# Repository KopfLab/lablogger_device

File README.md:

# *labLogger*

This repository holds the code, schematics, and documentation to build lab loggers. All content of this repository is free to use for noncommercial research and development efforts as outlined in the terms of the included [LICENSE file](LICENSE.md).

To cite ***labLogger*** in publications use:

> Kopf S, 2026. _labLogger: a Modular Internet Controllable LAB Equipment Logger_. <https://github.com/KopfLab/lablogger_device>

A BibTeX entry for LaTeX users is

```
@Manual{
  microLogger,
  title = {labLogger: a Modular Internet Controllable LAB Equipment Logger},
  author = {Sebastian Kopf},
  year = {2026},
  url = {https://github.com/KopfLab/lablogger_device}
}
```

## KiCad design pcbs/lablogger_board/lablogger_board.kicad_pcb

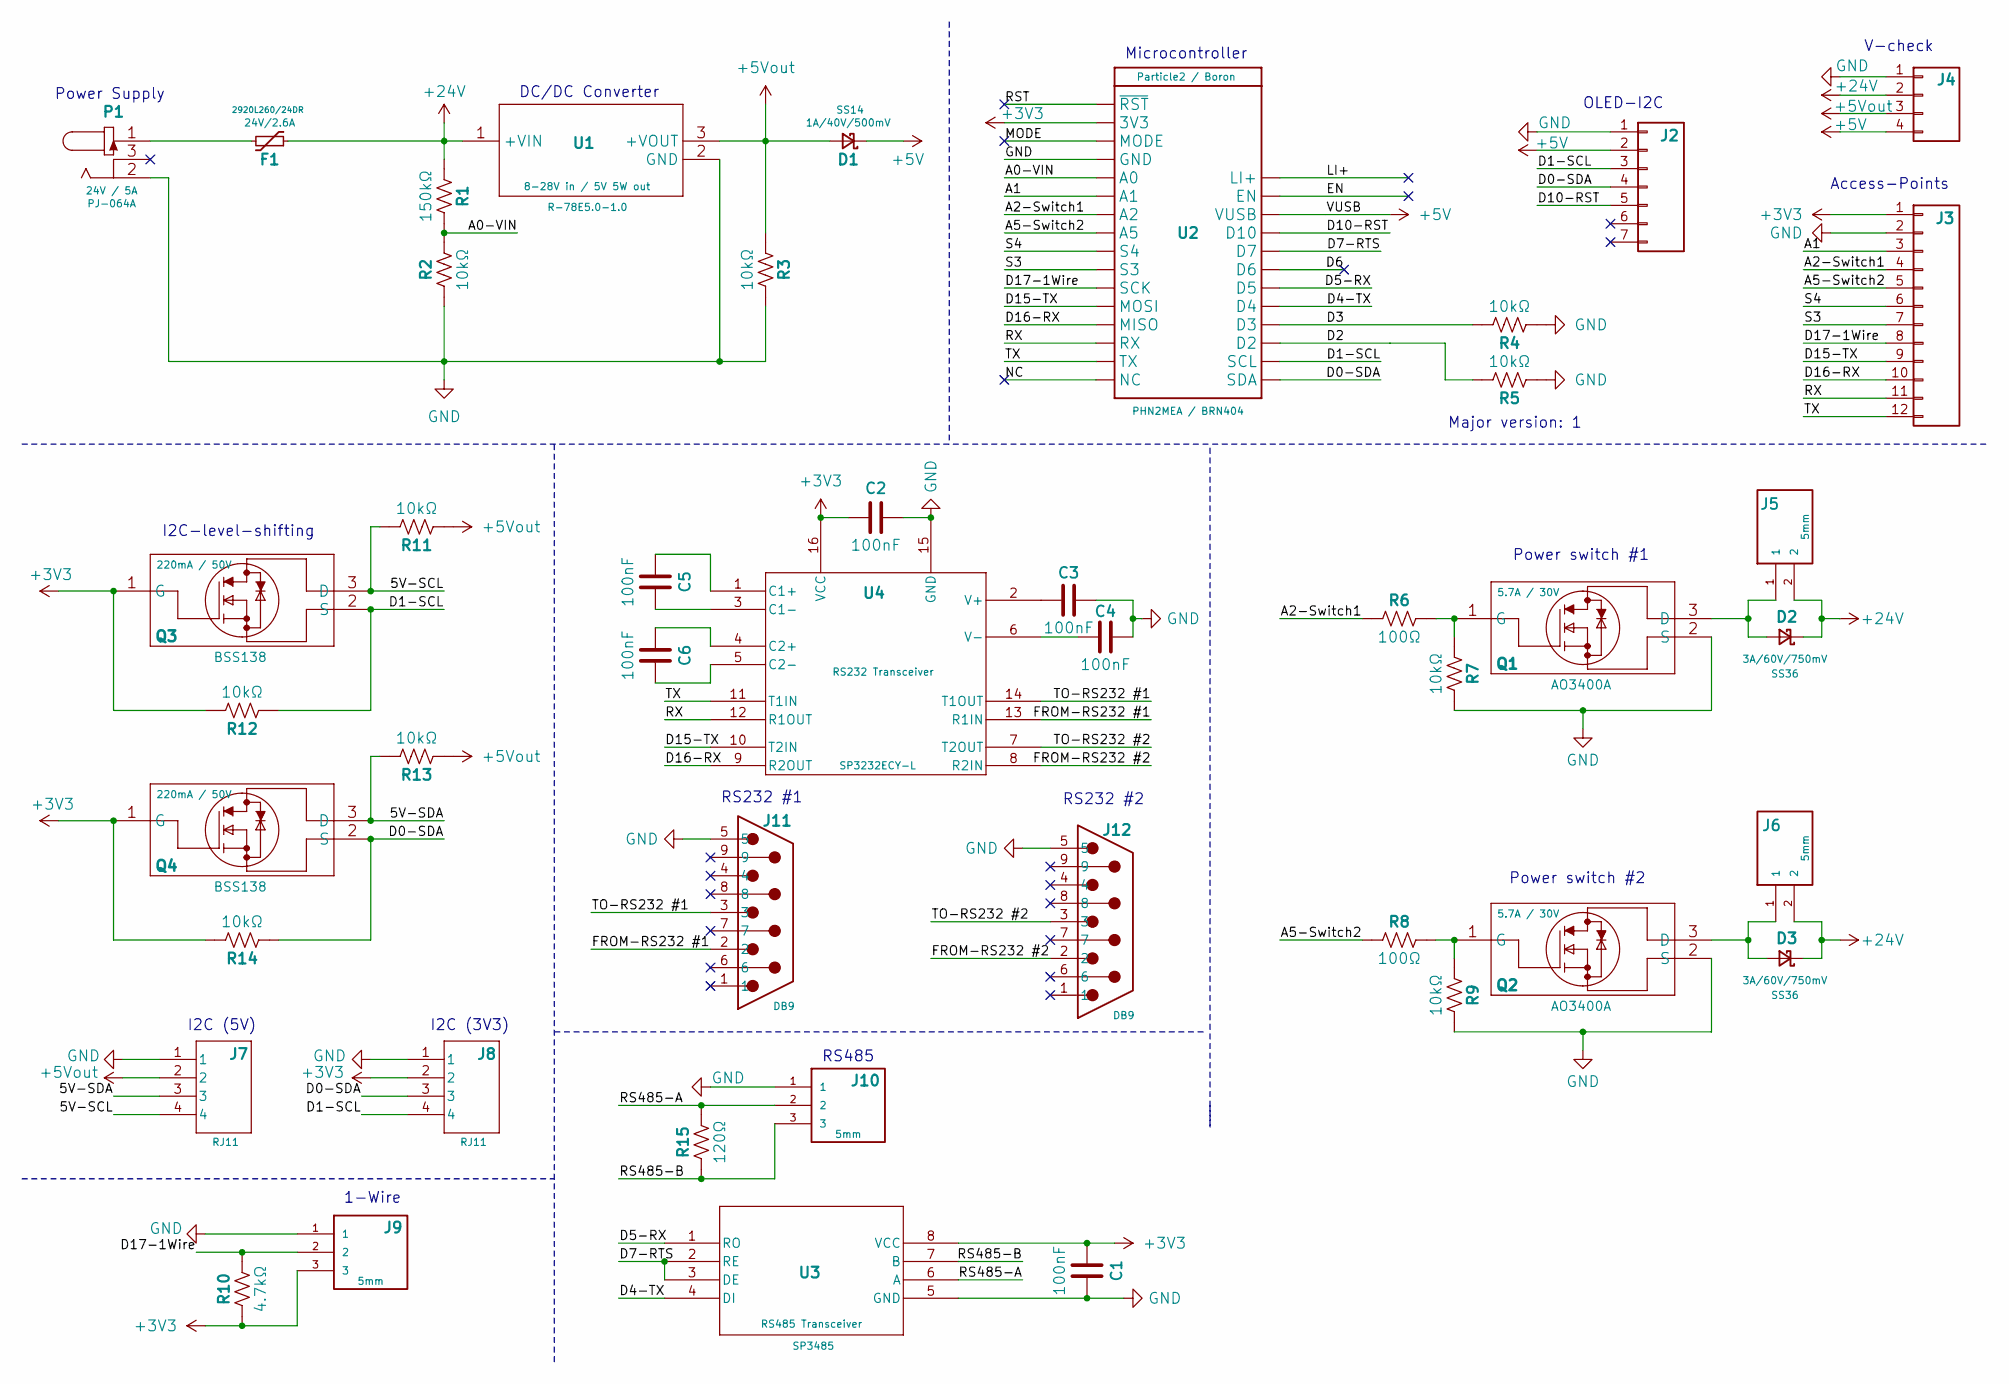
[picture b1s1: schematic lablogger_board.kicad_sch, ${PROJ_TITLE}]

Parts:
C1, C2, C3, C4, C6: 100nF; C_0603
C5: 100nF; C_0603; JLCPCB C1591
D1: 1A/40V/500mV; D_DO-214AC_SMA; MPN SS14; DigiKey SS14CT-ND
D2, D3: 3A/60V/750mV; D_DO-214AB_SMC; MPN SS36; DigiKey SS36FSCT-ND
F1: 24V/2.6A; Fuse_2920_7451; MPN 2920L260/24DR; DigiKey F6728CT-ND
J2: Conn_01x07; PIN_HEADERS_1X07
J3: Conn_01x12; PIN_HEADERS_1X12
J4: PINHD-1X4; PIN_HEADERS_1X04
J5, J6: 5mm; TERMINAL_BLOCK_1x02_5mm_vertical; MPN TBP04R2-500-02BE; DigiKey 2223-TBP04R2-500-02BE-ND
J7, J8: RJ11; RJ11_MOLEX_955032641; MPN 0955032641; DigiKey WM5579-ND
J9, J10: 5mm; TERMINAL_BLOCK_1x03_5mm_vertical; MPN TBP04R2-500-03BE; DigiKey 2223-TBP04R2-500-03BE-ND
J11, J12: DB9; DB9_male; MPN DE09P064TXLF; DigiKey 609-1524-ND
P1: 24V / 5A; PWR_JACK_PJ-064A; MPN PJ-064A; DigiKey CP-064A-ND
Q1, Q2: 5.7A / 30V; SOT-23-3; MPN AO3400A; DigiKey 785-1000-1-ND
Q3, Q4: 220mA / 50V; SOT-23-3; MPN BSS138; DigiKey BSS138CT-ND
R1: 150kΩ; R_1206; JLCPCB C17916
R2, R3, R4, R5, R7, R9, R12, R13, R14: 10kΩ; R_1206
R6, R8: 100Ω; R_1206; JLCPCB C17901
R10: 4.7kΩ; R_1206; JLCPCB C17936
R11: 10kΩ; R_1206; JLCPCB C17902
R15: 120Ω; R_1206; JLCPCB C17909
U1: 8-28V in / 5V 5W out; DC_DC_converter_R-78E5.0-1.0; MPN R-78E5.0-1.0; DigiKey 945-2201-ND
U2: Particle2 / Boron; PHOTON2; MPN PHN2MEA / BRN404
U3: RS485 Transceiver; 8-SOIC; MPN SP3485; DigiKey 1016-1817-1-ND
U4: RS232 Transceiver; TSSOP16_MXL; MPN SP3232ECY-L; DigiKey 1016-1105-5-ND

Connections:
+3V3: C1.1, C2.1, J3.1, J8.2, J9.3, Q3.1 (G), Q4.1 (G), R10.1, R12.2, R14.2, U2.2 (3V3), U3.8 (VCC), U4.16 (VCC)
+5V: D1.1 (K), J2.2, J4.4, U2.26 (VUSB)
+5Vout: D1.2 (A), J4.3, J7.2, R3.1, R11.1, R13.1, U1.3 (+VOUT)
+24V: D2.1 (K), D3.1 (K), F1.1, J4.2, J5.2, J6.2, R1.1, U1.1 (+VIN)
/5V-SCL: J7.4, Q3.3 (D), R11.2
/5V-SDA: J7.3, Q4.3 (D), R13.2
/A0-VIN: R1.2, R2.2, U2.5 (A0)
/A1: J3.3, U2.6 (A1)
/A2-Switch1: J3.4, R6.1, U2.7 (A2)
/A5-Switch2: J3.5, R8.1, U2.8 (A5)
/D0-SDA: J2.4, J8.3, Q4.2 (S), R14.1, U2.17 (SDA)
/D1-SCL: J2.3, J8.4, Q3.2 (S), R12.1, U2.18 (SCL)
/D2: R5.2, U2.19 (D2)
/D3: R4.2, U2.20 (D3)
/D4-TX: U2.21 (D4), U3.4 (DI)
/D5-RX: U2.22 (D5), U3.1 (RO)
/D6: U2.23 (D6)
/D7-RTS: U2.24 (D7), U3.2 (RE), U3.3 (DE)
/D10-RST: J2.5, U2.25 (D10)
/D15-TX: J3.9, U2.12 (MOSI), U4.10 (T2IN)
/D16-RX: J3.10, U2.13 (MISO), U4.9 (R2OUT)
/D17-1Wire: J3.8, J9.2, R10.2, U2.11 (SCK)
/EN: U2.27 (EN)
/FROM-RS232 #1: J11.2, U4.13 (R1IN)
/FROM-RS232 #2: J12.2, U4.8 (R2IN)
/LI+: U2.28 (LI+)
/MODE: U2.3 (MODE)
/NC: U2.16 (NC)
/RS485-A: J10.2, R15.2, U3.6 (A)
/RS485-B: J10.3, R15.1, U3.7 (B)
/RST: U2.1 (~RST)
/RX: J3.11, U2.14 (RX), U4.12 (R1OUT)
/S3: J3.7, U2.10 (S3)
/S4: J3.6, U2.9 (S4)
/TO-RS232 #1: J11.3, U4.14 (T1OUT)
/TO-RS232 #2: J12.3, U4.7 (T2OUT)
/TX: J3.12, U2.15 (TX), U4.11 (T1IN)
GND: C1.2, C2.2, C3.2, C4.2, J2.1, J3.2, J4.1, J7.1, J8.1, J9.1, J10.1, J11.5, J12.5, P1.2, Q1.2 (S), Q2.2 (S), R2.1, R3.2, R4.1, R5.1, R7.2, R9.2, U1.2 (GND), U2.4 (GND), U3.5 (GND), U4.15 (GND)
unnamed: D2.2 (A), J5.1, Q1.3 (D)
unnamed: D3.2 (A), J6.1, Q2.3 (D)
unnamed: F1.2, P1.1
unnamed: Q1.1 (G), R6.2, R7.1
unnamed: Q2.1 (G), R8.2, R9.1
unnamed: C5.1, U4.1 (C1+)
unnamed: C5.2, U4.3 (C1-)
unnamed: C6.1, U4.4 (C2+)
unnamed: C6.2, U4.5 (C2-)
unnamed: C3.1, U4.2 (V+)
unnamed: C4.1, U4.6 (V-)

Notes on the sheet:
Major version: 1
I2C (3V3)
Power switch #1
Microcontroller
Power Supply
1-Wire
I2C (5V)
DC/DC Converter
RS485
Access-Points
RS232 #2
RS232 #1
V-check
Power switch #2
I2C-level-shifting
OLED-I2C

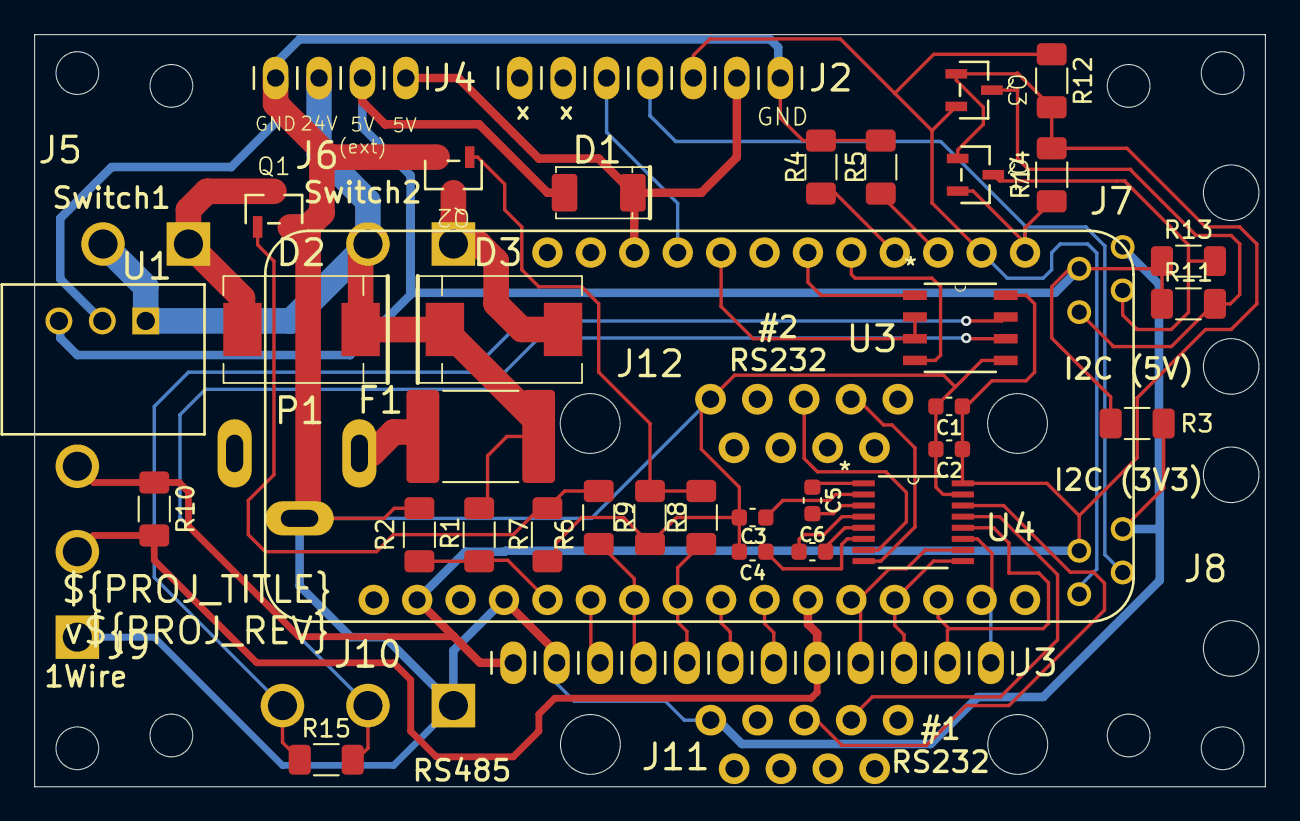
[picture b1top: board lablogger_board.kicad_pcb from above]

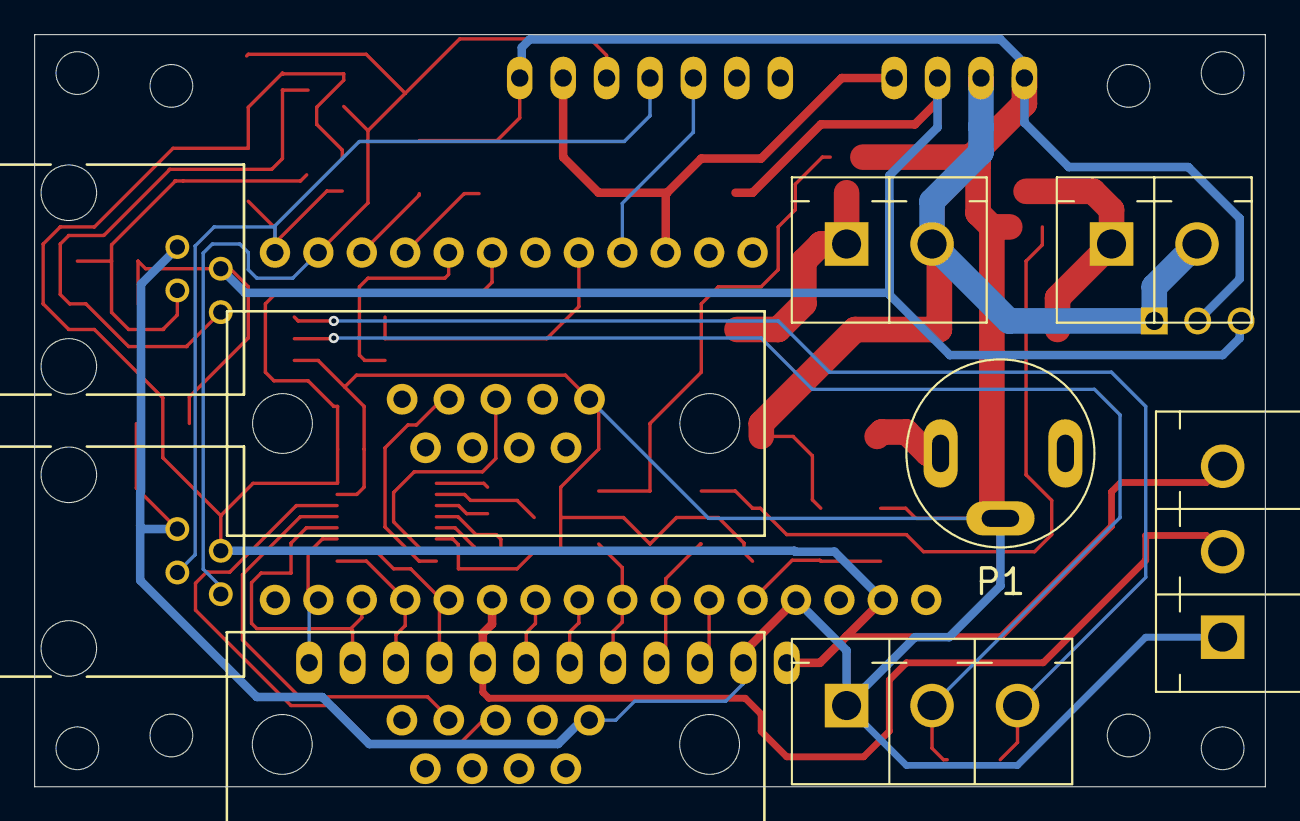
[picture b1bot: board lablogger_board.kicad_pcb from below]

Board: 2 copper layers, 72.0 x 44.0 mm, 53 parts (9 on the bottom side), 43 nets.

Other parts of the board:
H1, H2, H3, H4, H5, H6, H7, H8: MountingHole_2.5mm_M2.5

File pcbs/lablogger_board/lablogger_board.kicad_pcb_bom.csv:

Designator,Quantity,Value,Footprint,Package,MPN,DNP,Mount_Type,Description,JLCPCB,JLCPCBURL,DigiKey,DigiKeyURL,STANDARD,MAXIMUM_PACKAGE_HEIGHT,MANUFACTURER,ParticleURL
"C1, C2, C3, C4, C5, C6",6,100nF,C_0603,,,,smt,Unpolarized capacitor,C1591,https://jlcpcb.com/partdetail/1943-CL10B104KB8NNNC/C1591,,,,,,
D1,1,1A/40V/500mV,D_DO-214AC_SMA,,SS14,,smt,Diode 40 V 1A Surface Mount DO-214AC (SMA),C83852,https://jlcpcb.com/partdetail/onsemi-SS14/C83852,SS14CT-ND,https://www.digikey.com/en/products/detail/onsemi/SS14/965474,,,,
"D2, D3",2,3A/60V/750mV,D_DO-214AB_SMC,,SS36,,tht,Diode 60 V 3A Surface Mount DO-214AB (SMC),C391251,https://jlcpcb.com/partdetail/onsemi-SS36/C391251,SS36FSCT-ND,https://www.digikey.com/en/products/detail/onsemi/SS36/1053019,,,,
F1,1,24V/2.6A,Fuse_1812,,2920L260/24DR,,smt,"Polymeric PTC Resettable Fuse 24V 2.6 A Ih Surface Mount 2920 (7351 Metric), Concave",C315904 ,https://jlcpcb.com/partdetail/Littelfuse-2920L26024DR/C315904,F6728CT-ND,https://www.digikey.com/en/products/detail/littelfuse-inc/29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,,,,
"J10, J9",2,5mm,TERMINAL_BLOCK_1x03_5mm_vertical,,TBP04R2-500-03BE,,tht,"3 Position Terminal Block Header, Male Pins, Shrouded (4 Side) 0.197"" (5.00mm) Vertical Through Hole",,,2223-TBP04R2-500-03BE-ND,https://www.digikey.com/en/products/detail/same-sky-formerly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,Manufacturer Recommendations,12.00mm,,
"J11, J12",2,DB9,DB9_male,,DE09P064TXLF,,tht,"9 Position D-Sub Plug, Male Pins Connector",,,609-1524-ND,https://www.digikey.com/en/products/detail/amphenol-cs-fci/D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,,,,
J2,1,Conn_01x07,PIN_HEADERS_1X07,,,,tht,"Basic 0.1"" PTH",,,,,,,,
J3,1,Conn_01x12,PIN_HEADERS_1X12,,,,tht,"Basic 0.1"" PTH",,,,,,,,
J4,1,PINHD-1X4,PIN_HEADERS_1X04,,,,tht,"Basic 0.1"" PTH",,,,,,,,
"J5, J6",2,5mm,TERMINAL_BLOCK_1x02_5mm_vertical,,TBP04R2-500-02BE,,tht,"2 Position Terminal Block Header, Male Pins, Shrouded (4 Side) 0.197"" (5.00mm) Vertical Through Hole",,,2223-TBP04R2-500-02BE-ND,https://www.digikey.com/en/products/detail/same-sky-formerly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,,12.00mm,CUI Devices,
"J7, J8",2,RJ11,RJ11_MOLEX_955032641,,0955032641,,tht,"Jack Modular Connector 6p4c (RJ11, RJ14) Vertical Unshielded Cat3",,,WM5579-ND,https://www.digikey.com/en/products/detail/molex/0955032641/1835871,,,,
P1,1,24V / 5A,PWR_JACK_PJ-064A,,PJ-064A,,tht,"2.0 mm Center Pin, 5.0 A, Vertical, Panel Mount, PC Pins, Dc Power Jack Connector",,,CP-064A-ND,https://www.digikey.com/en/products/detail/cui-devices/PJ-06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,,,,
"Q1, Q2",2,5.7A / 30V,SOT-23-3,,AO3400A,,tht,N-Channel 30 V 5.7A (Ta) 1.4W (Ta) Surface Mount SOT-23-3,C20917,https://jlcpcb.com/partdetail/Alpha_OmegaSemicon-AO3400A/C20917,785-1000-1-ND,https://www.digikey.com/en/products/detail/alpha-omega-semic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,,,,
"Q3, Q4",2,220mA / 50V,SOT-23-3,,BSS138,,tht,N-Channel 50 V 2200mA 350mW (Ta) Surface Mount SOT-23-3,C52895,https://jlcpcb.com/partdetail/onsemi-BSS138/C52895,BSS138CT-ND,https://www.digikey.com/en/products/detail/onsemi/BSS138/244210,,,,
R1,1,150kΩ,R_1206,,,,smt,"Resistor, US symbol",C17916,https://jlcpcb.com/partdetail/18604-1206W4F1503T5E/C17916,,,,,,
R10,1,4.7kΩ,R_1206,,,,smt,"Resistor, US symbol",C17936,https://jlcpcb.com/partdetail/18624-1206W4F4701T5E/C17936,,,,,,
"R11, R12, R13, R14, R2, R3, R4, R5, R7, R9",10,10kΩ,R_1206,,,,smt,"Resistor, US symbol",C17902,https://jlcpcb.com/partdetail/18590-1206W4F1002T5E/C17902,,,,,,
R15,1,120Ω,R_1206,,,,smt,"Resistor, US symbol",C17909,https://jlcpcb.com/partdetail/18597-1206W4F1200T5E/C17909,,,,,,
"R6, R8",2,100Ω,R_1206,,,,smt,"Resistor, US symbol",C17901 ,https://jlcpcb.com/partdetail/18589-1206W4F1000T5E/C17901,,,,,,
U1,1,8-28V in / 5V 5W out,DC_DC_converter_R-78E5.0-1.0,,R-78E5.0-1.0,,tht,Linear Regulator Replacement DC DC Converter 1 Output 5V 1A 8V - 28V Input,,,945-2201-ND,https://www.digikey.com/en/products/detail/recom-power/R-78E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,,,,
U2,1,Particle2 / Boron,PHOTON2,,PHN2MEA / BRN404,,tht,Particle Photon 2 Wi-Fi enabled development kit,,,,,,,,https://store.particle.io/collections/wifi/products/photon-2
U3,1,RS485 Transceiver,8-SOIC,,SP3485,,smt,"1/1 Transceiver Half RS422, RS485 8-SOIC",C8963,https://jlcpcb.com/partdetail/MaxLinear-SP3485EN_LTR/C8963,1016-1817-1-ND,https://www.digikey.com/en/products/detail/maxlinear-inc/SP3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,,,,
U4,1,RS232 Transceiver,TSSOP16_MXL,,SP3232ECY-L,,smt,2/2 Transceiver Full RS232 16-TSSOP,C3028967,https://jlcpcb.com/partdetail/MaxLinear-SP3232ECY_LTR/C3028967,1016-1105-5-ND,https://www.digikey.com/en/products/detail/maxlinear-inc/SP3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,,,,

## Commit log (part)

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2026-05-01 lablogger pcb first draft
2026-05-02 lablogger first version
2026-05-29 add footprints
2026-05-29 basic repo setup for device firmware
2026-05-29 initial timed switch
2026-05-30 add aditional library submodules
2026-05-30 implement basic lablogger hardware
2026-05-30 implement timed switch program
2026-05-31 fix program root path
2026-05-31 change src to aux
2026-06-02 fix time switch
2026-06-02 update pcb to version 0.3: make holes for db9 connectors bigger

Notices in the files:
pcbs/lablogger_board/lablogger_board.kicad_sch:
https://creativecommons.org/licenses/by-sa/4.0
Released under the Creative Commons Share-Alike 4.0 License
